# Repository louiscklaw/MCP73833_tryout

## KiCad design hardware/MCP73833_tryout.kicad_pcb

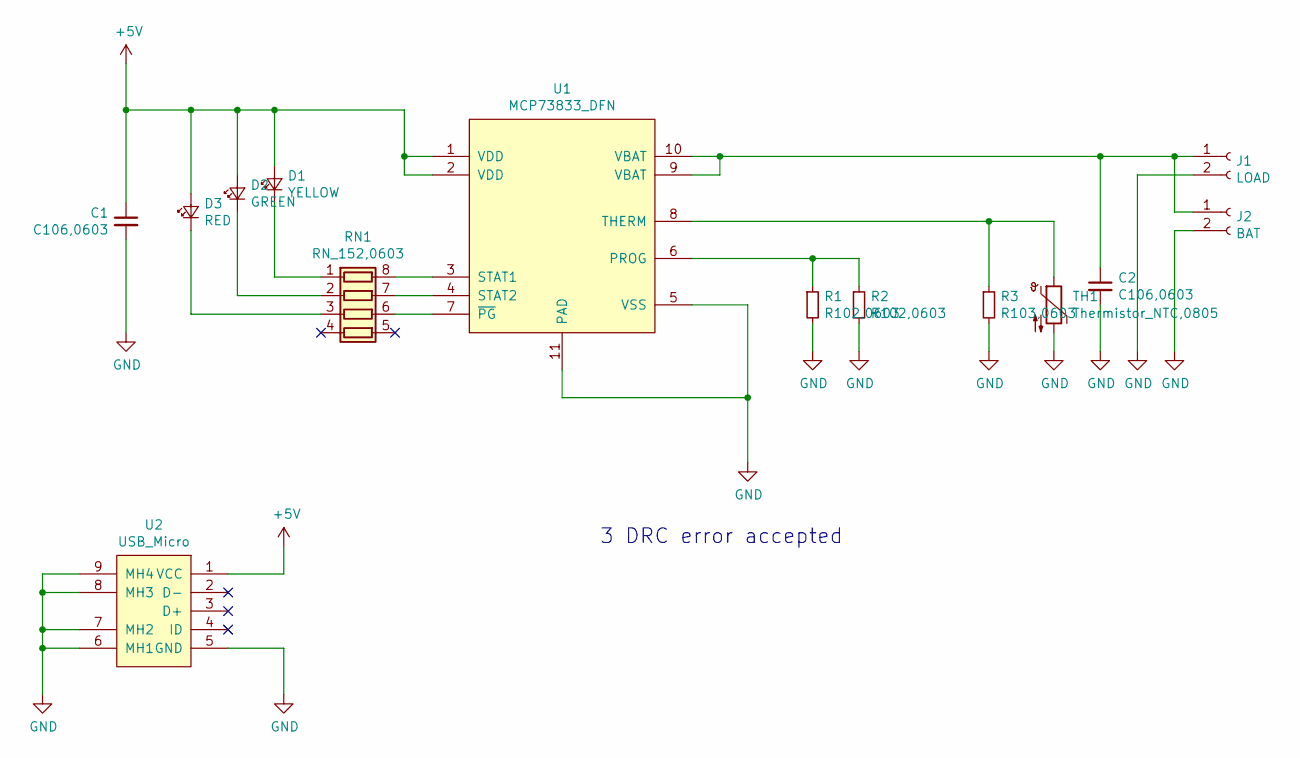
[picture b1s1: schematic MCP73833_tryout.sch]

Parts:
C1, C2: C106,0603; C_0603_1608Metric_Pad1.05x0.95mm_HandSolder
D1: YELLOW; LED_0603_1608Metric
D2: GREEN; LED_0603_1608Metric
D3: RED; LED_0603_1608Metric
J1: LOAD; PinHeader_1x02_P2.54mm_Vertical
J2: BAT; PinHeader_1x02_P2.54mm_Vertical
R1, R2: R102,0603; R_0603_1608Metric_Pad1.05x0.95mm_HandSolder
R3: R103,0603; R_0603_1608Metric_Pad1.05x0.95mm_HandSolder
RN1: RN_152,0603; R_Array_Concave_4x0603
TH1: Thermistor_NTC,0805; r_0805
U1: MCP73833_DFN
U2: USB_Micro; USB_Micro-B_Molex-105017-0001

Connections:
+5V: C1.1, D1.2 (A), D2.2 (A), D3.2 (A), U1.1 (VDD), U1.2 (VDD), U2.1 (VCC)
GND: C1.2, C2.2, J1.2, J2.2, R1.2, R2.2, R3.2, TH1.2, U1.5 (VSS), U1.11 (PAD), U2.5 (GND), U2.6 (MH1), U2.7 (MH2), U2.8 (MH3), U2.9 (MH4)
unnamed: C2.1, J1.1, J2.1, U1.9 (VBAT), U1.10 (VBAT)
unnamed: D1.1 (K), RN1.1 (R1.1)
unnamed: D2.1 (K), RN1.2 (R2.1)
unnamed: D3.1 (K), RN1.3 (R3.1)
unnamed: R1.1, R2.1, U1.6 (PROG)
unnamed: R3.1, TH1.1, U1.8 (THERM)
unnamed: RN1.6 (R3.2), U1.7 (~PG~)
unnamed: RN1.7 (R2.2), U1.4 (STAT2)
unnamed: RN1.8 (R1.2), U1.3 (STAT1)

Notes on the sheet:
3 DRC error accepted

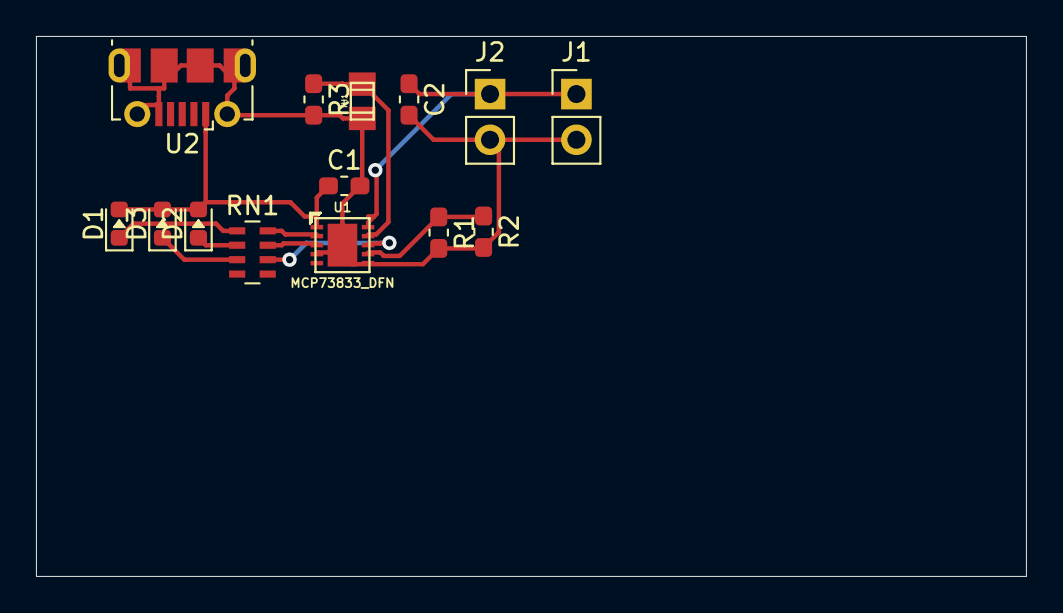
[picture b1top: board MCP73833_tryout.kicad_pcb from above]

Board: 2 copper layers, 55.0 x 30.0 mm, 14 parts (0 on the bottom side), 11 nets.

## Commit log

2019-06-13 update,
2019-06-14 udpate,
2019-06-14 update for MCP73833 DFN,
2020-05-06 ci: init travis token,
2020-05-06 ci: init travis build config,
